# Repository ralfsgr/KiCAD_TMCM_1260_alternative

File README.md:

# KiCAD_TMCM_1260_alternative
KiCad

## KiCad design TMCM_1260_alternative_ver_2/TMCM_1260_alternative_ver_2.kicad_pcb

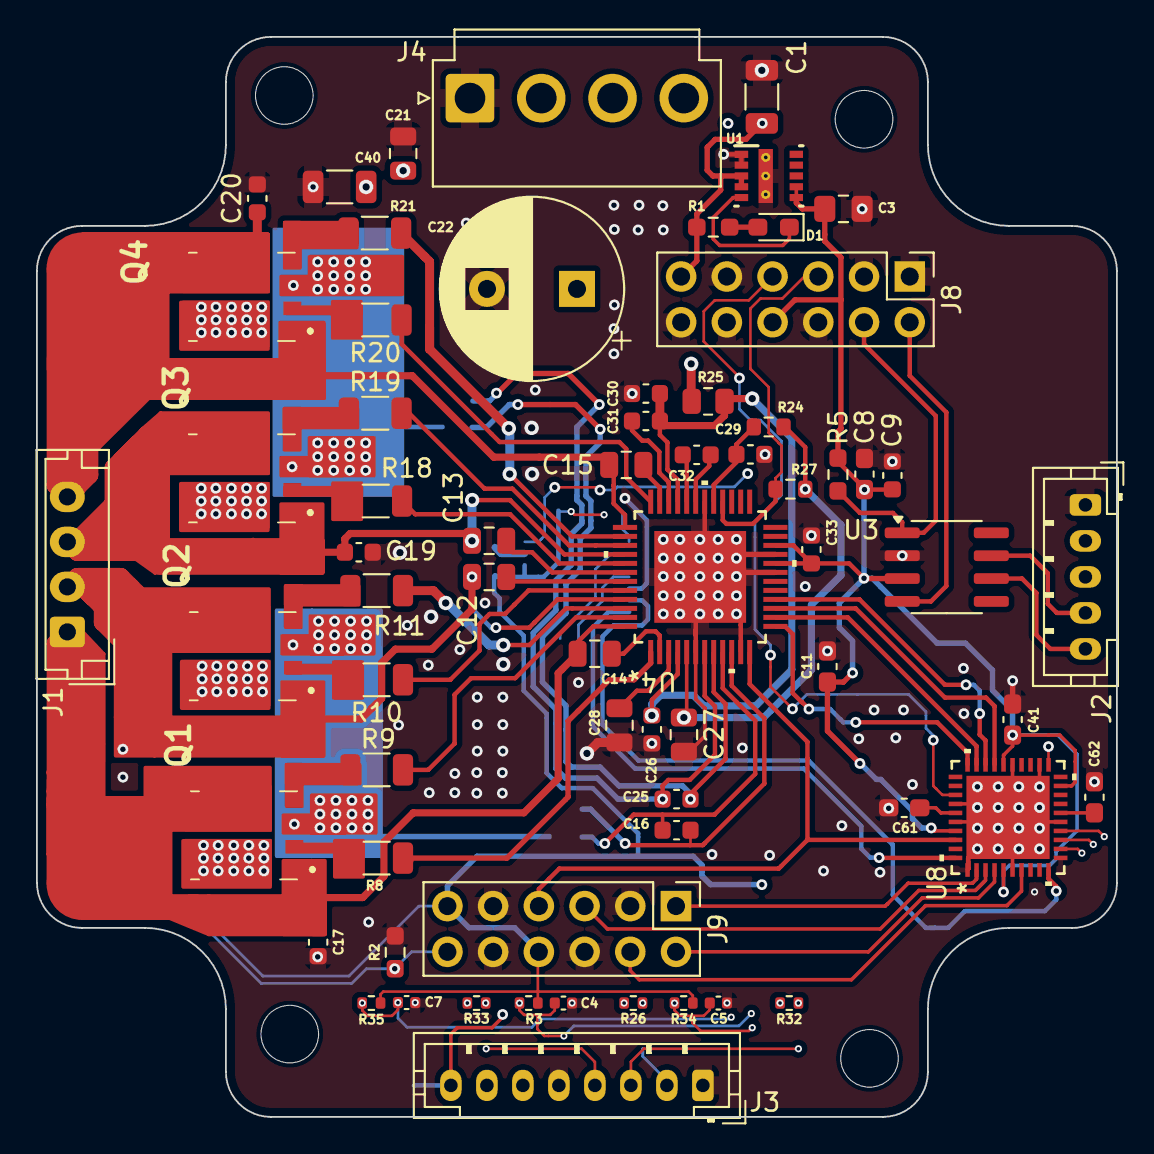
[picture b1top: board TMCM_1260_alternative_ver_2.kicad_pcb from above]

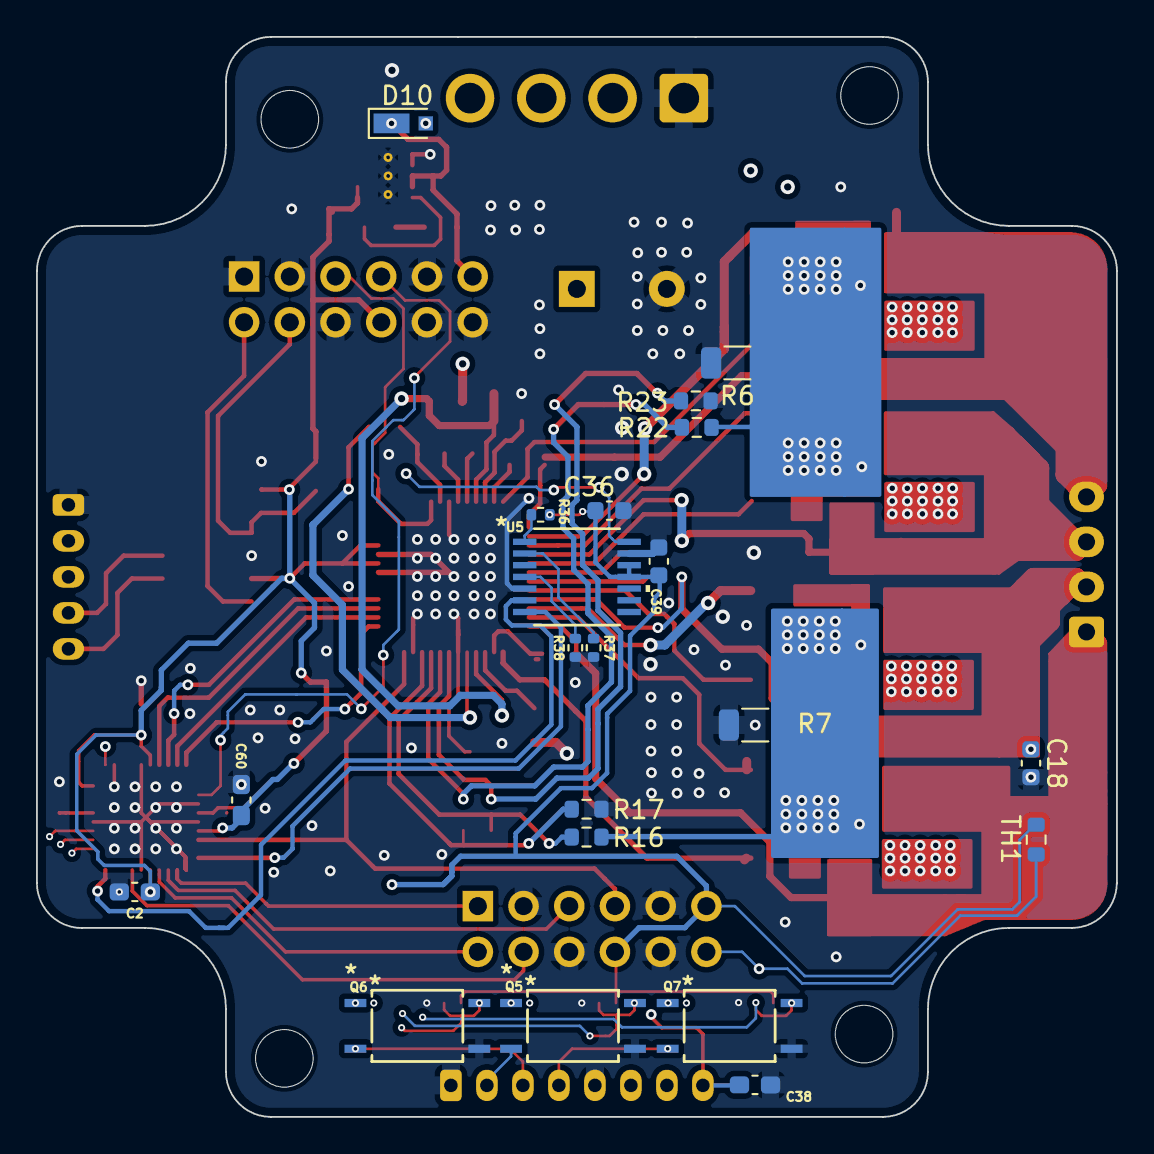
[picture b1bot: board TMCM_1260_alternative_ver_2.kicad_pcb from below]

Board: 4 copper layers, 60.0 x 60.0 mm, 87 parts (21 on the bottom side), 76 nets.

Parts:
C1: 10uF; C_1206_3216Metric
C2, C8, C11, C38, C41, C60, C61, C62: 0.1u; C_0603_1608Metric_Pad1.08x0.95mm_HandSolder
C3: 33uF; C_0805_2012Metric_Pad1.18x1.45mm_HandSolder
C4, C5, C7: 0.1u; C_0402_1005Metric
C9, C39: 1u; C_0603_1608Metric
C12, C13, C14, C15: 470nF; C_0805_2012Metric
C16, C25: 2n2; C_0603_1608Metric
C17, C18, C19, C20: 1n, 100V; C_0603_1608Metric
C21: 4u7; C_0805_2012Metric
C22: 330u; CP_Radial_D10.0mm_P5.00mm
C26, C36: 100n; C_0603_1608Metric
C27, C28: 10u; C_0805_2012Metric
C29, C30, C33: 470n; C_0603_1608Metric
C31: 100n, 16V; C_0603_1608Metric
C32: 22n, 100V; C_0603_1608Metric
C40: 47u; C_1206_3216Metric
D1: LED_RED; D_0603_1608Metric_Pad1.05x0.95mm_HandSolder
D10: D_Schottky; D_MicroSMP_AK
J1: Motor; JST_EH_B4B-EH-A_1x04_P2.50mm_Vertical
J2: CAN; JST_PH_B5B-PH-K_1x05_P2.00mm_Vertical
J3: I/O; JST_PH_B8B-PH-K_1x08_P2.00mm_Vertical
J4: Power; JST_VH_B4P-VH_1x04_P3.96mm_Vertical
J8, J9: Conn_02x06_Odd_Even; PinHeader_2x06_P2.54mm_Vertical
Q1, Q2, Q3, Q4: NVMFD5C650NLT1G; NVMFD5C446NLWFT1G
Q5, Q6, Q7: TLP185GR-TPL_SE; TLP185_GR_TPL_SE
R1: 2k; R_0603_1608Metric_Pad0.98x0.95mm_HandSolder
R2: 10k; R_0603_1608Metric_Pad0.98x0.95mm_HandSolder
R3, R34, R35, R36, R37, R38: 4k7; R_0402_1005Metric
R5: 4k7; R_0603_1608Metric_Pad0.98x0.95mm_HandSolder
R6, R7: 0.075; R_1206_3216Metric
R8, R9, R10, R11, R18, R19, R20, R21: 15; R_1206_3216Metric
R16, R17, R22, R23: 47; R_0603_1608Metric
R24: 2R2; R_0603_1608Metric
R25: 1R; R_0805_2012Metric
R26, R32, R33: 24k; R_0402_1005Metric
R27: 4k7; R_0603_1608Metric
TH1: Thermistor_NTC; R_0603_1608Metric
U1: LMZM23600V3SILR
U3: TCAN337; SOIC-8_3.9x4.9mm_P1.27mm
U4: TMC5160A-TA-T; TMC5160A_TA_T
U5: AS5047P-ATSM; AS5047P_ATSM
U8: TMC4361A-LA-T; TMC4361A_LA_T

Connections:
5VOUT: C27.1, C38.1, J3.8, R24.1, R27.1, U4.5 (5VOUT)
12-36V: C21.1, C22.1, C40.1, D10.2 (A), J3.6, J3.7, J4.2, J4.3, Q1.7 (D1_1), Q1.8 (D1_2), Q1.9 (D1_3), Q1.10 (D1_4), Q1.14, Q2.7 (D1_1), Q2.8 (D1_2), Q2.9 (D1_3), Q2.10 (D1_4), Q2.14, Q3.7 (D1_1), Q3.8 (D1_2), Q3.9 (D1_3), Q3.10 (D1_4), Q3.14, Q4.7 (D1_1), Q4.8 (D1_2), Q4.9 (D1_3), Q4.10 (D1_4), Q4.14, R25.1, R26.2, R32.2, R33.2
/CANH: J2.4, U3.7 (CANH)
/CANL: J2.5, U3.6 (CANL)
/RXD: J8.2, U3.4 (RXD)
/TXD: J8.4, R5.1, U3.1 (TXD)
BMA1: C13.2, C19.1, J1.3, Q3.1 (S1), Q3.5 (D2_1), Q3.6 (D2_2), Q3.11 (D2_3), Q3.12 (D2_4), Q3.13, U4.40 (BMA1)
BMA2: C15.2, C20.1, J1.4, Q4.1 (S1), Q4.5 (D2_1), Q4.6 (D2_2), Q4.11 (D2_3), Q4.12 (D2_4), Q4.13, U4.37 (BMA2)
BMB1: C14.2, C17.1, J1.1, Q1.1 (S1), Q1.5 (D2_1), Q1.6 (D2_2), Q1.11 (D2_3), Q1.12 (D2_4), Q1.13, U4.48 (BMB1)
BMB2: C12.2, C18.1, J1.2, Q2.1 (S1), Q2.5 (D2_1), Q2.6 (D2_2), Q2.11 (D2_3), Q2.12 (D2_4), Q2.13, U4.45 (BMB2)
CA1: C13.1, U4.42 (CA1)
CA2: C15.1, U4.35 (CA2)
CB1: C14.1, U4.2 (CB1)
CB2: C12.1, U4.43 (CB2)
CLK_EXT: J9.7, U4.12 (CLK), U8.38 (CLK_EXT)
CPI: C32.1, U4.32 (CPI)
CPO: C32.2, U4.31 (CPO)
CSN: J9.1, U8.2 (NSCSIN)
CSN_DRV: U4.13 (CSN_CFG3), U8.30 (NSCSDRV_SDO)
DRV_ENN: J8.5, R27.2, U4.28 (DRV_ENN)
GND: C1.2, C2.2, C3.2, C4.2, C5.2, C7.2, C8.2, C9.2, C11.2, C17.2, C18.2, C19.2, C20.2, C21.2, C22.2, C26.2, C27.2, C28.2, C29.2, C30.1, C33.2, C36.1, C38.2, C39.1, C40.2, C41.1, C60.1, C61.1, C62.1, J2.1, J3.1, J3.5, J4.1, J8.1, J8.3, J8.6, J8.9, J8.10, J8.12, J9.3, J9.6, J9.9, J9.10, Q5.4, Q6.4, Q7.4, R2.1, R6.2, R7.2, R17.1, R23.1, R37.2, R38.2, U1.1 (GND), U1.2 (MODE_SYNC), U1.11 (PAD), U1.PAD, U3.2 (GND), U4.6 (GNDA), U4.11 (TST_MODE), U4.19 (GNDD), U4.21 (SD_MODE), U4.30 (GNDD), U4.49 (GNDD/GNDP), U5.5 (TEST), U5.13 (GND), U8.1 (ANEG_NSCLK), U8.6 (GND), U8.11 (BNEG_NSDI), U8.15 (GND), U8.22 (NNEG), U8.25 (GND), U8.34 (TEST_MODE), U8.36 (GND), U8.41
HA1: R18.1, U4.41 (HA1)
HA2: R20.1, U4.36 (HA2)
HB1: R8.1, U4.1 (HB1)
HB2: R10.1, U4.44 (HB2)
HOME_REF: C4.1, Q5.6, R3.1, U8.13 (HOME_REF)
INCR_A: U5.7 (A), U8.40 (A_SCLK)
INCR_B: U5.6 (B), U8.10 (B_SDI)
INCR_I: U5.14 (I/PWM), U8.21 (N)
INTR: J8.7, U8.33 (INTR)
LA1: R19.1, U4.39 (LA1)
LA2: R21.1, U4.38 (LA2)
LB1: R9.1, U4.47 (LB1)
LB2: R11.1, U4.46 (LB2)
unnamed: C61.2, U8.35 (VDD1V8)
unnamed: C62.2, U8.16 (VDD1V8)
unnamed: D1.2 (A), R1.1
unnamed: D1.1 (K), U1.5 (PGOOD)
unnamed: Q1.2 (G1), R8.2
unnamed: Q1.4 (G2), R9.2
unnamed: Q1.3 (S2), Q2.3 (S2), R7.1, R16.1
unnamed: Q2.2 (G1), R10.2
unnamed: Q2.4 (G2), R11.2
unnamed: Q3.2 (G1), R18.2
unnamed: Q3.4 (G2), R19.2
unnamed: Q3.3 (S2), Q4.3 (S2), R6.1, R22.1
unnamed: Q4.2 (G1), R20.2
unnamed: Q4.4 (G2), R21.2
unnamed: Q5.1, R26.1
unnamed: Q6.1, R32.1
unnamed: Q7.1, R33.1
unnamed: C28.1, U4.3 (12VOUT)
unnamed: C29.1, R24.2, U4.29 (VCC)
unnamed: R37.1, U5.2 (CLK)
unnamed: R36.1, U5.1 (CSn)
unnamed: R38.1, U5.4 (MOSI)
Out_1: J3.4, Q7.3
Out_2: J3.3, Q6.3
PGOOD: C1.1, D10.1 (K), J8.11, R1.2, U1.3 (VIN), U1.4 (EN)
SCK: J9.5, U8.3 (SCKIN)
SCK_DRV: U4.14 (SCK_CFG2), U8.29 (SCKDRV_NSDO)
SPI_MISO: J9.4, U8.7 (SDOIN)
SPI_MISO_DRV: U4.16 (SDO_CFG0), U8.28 (SDIDRV_NSCLK)
SPI_MOSI: J9.2, U8.4 (SDIIN)
SPI_MOSI_DRV: U4.15 (SDI_CFG1), U8.27 (SDODRV_SCLK)
SRAH: C25.1, R22.2, U4.8 (SRAH)
SRAL: C25.2, R23.2, U4.7 (SRAL)
SRBH: C16.1, R16.2, U4.9 (SRBH)
SRBL: C16.2, R17.2, U4.10 (SRBL)
STOPL: C7.1, Q7.6, R35.1, U8.12 (STOPL)
STOPR: C5.1, Q6.6, R34.1, U8.14 (STOPR)
VCC_IO: C2.1, C3.1, C8.1, C9.1, C11.1, C33.1, C36.2, C39.2, C41.2, C60.2, J8.8, J9.8, J9.11, R3.2, R5.2, R34.2, R35.2, R36.2, TH1.2, U1.6 (VOUT), U1.7 (FB), U3.3 (VCC), U4.20 (VCC_IO), U4.22 (SPI_MODE), U5.11 (VDD), U5.12 (VDD3V), U8.5 (VCC), U8.19 (NFREEZE), U8.26 (VCC), U8.37 (VCC)
VCP: C31.2, U4.34 (VCP)
VS: C26.1, C30.2, C31.1, R25.2, U4.4 (VSA), U4.33 (VS)
home: J3.2, Q5.3
monitoring: J9.12, R2.2, TH1.1

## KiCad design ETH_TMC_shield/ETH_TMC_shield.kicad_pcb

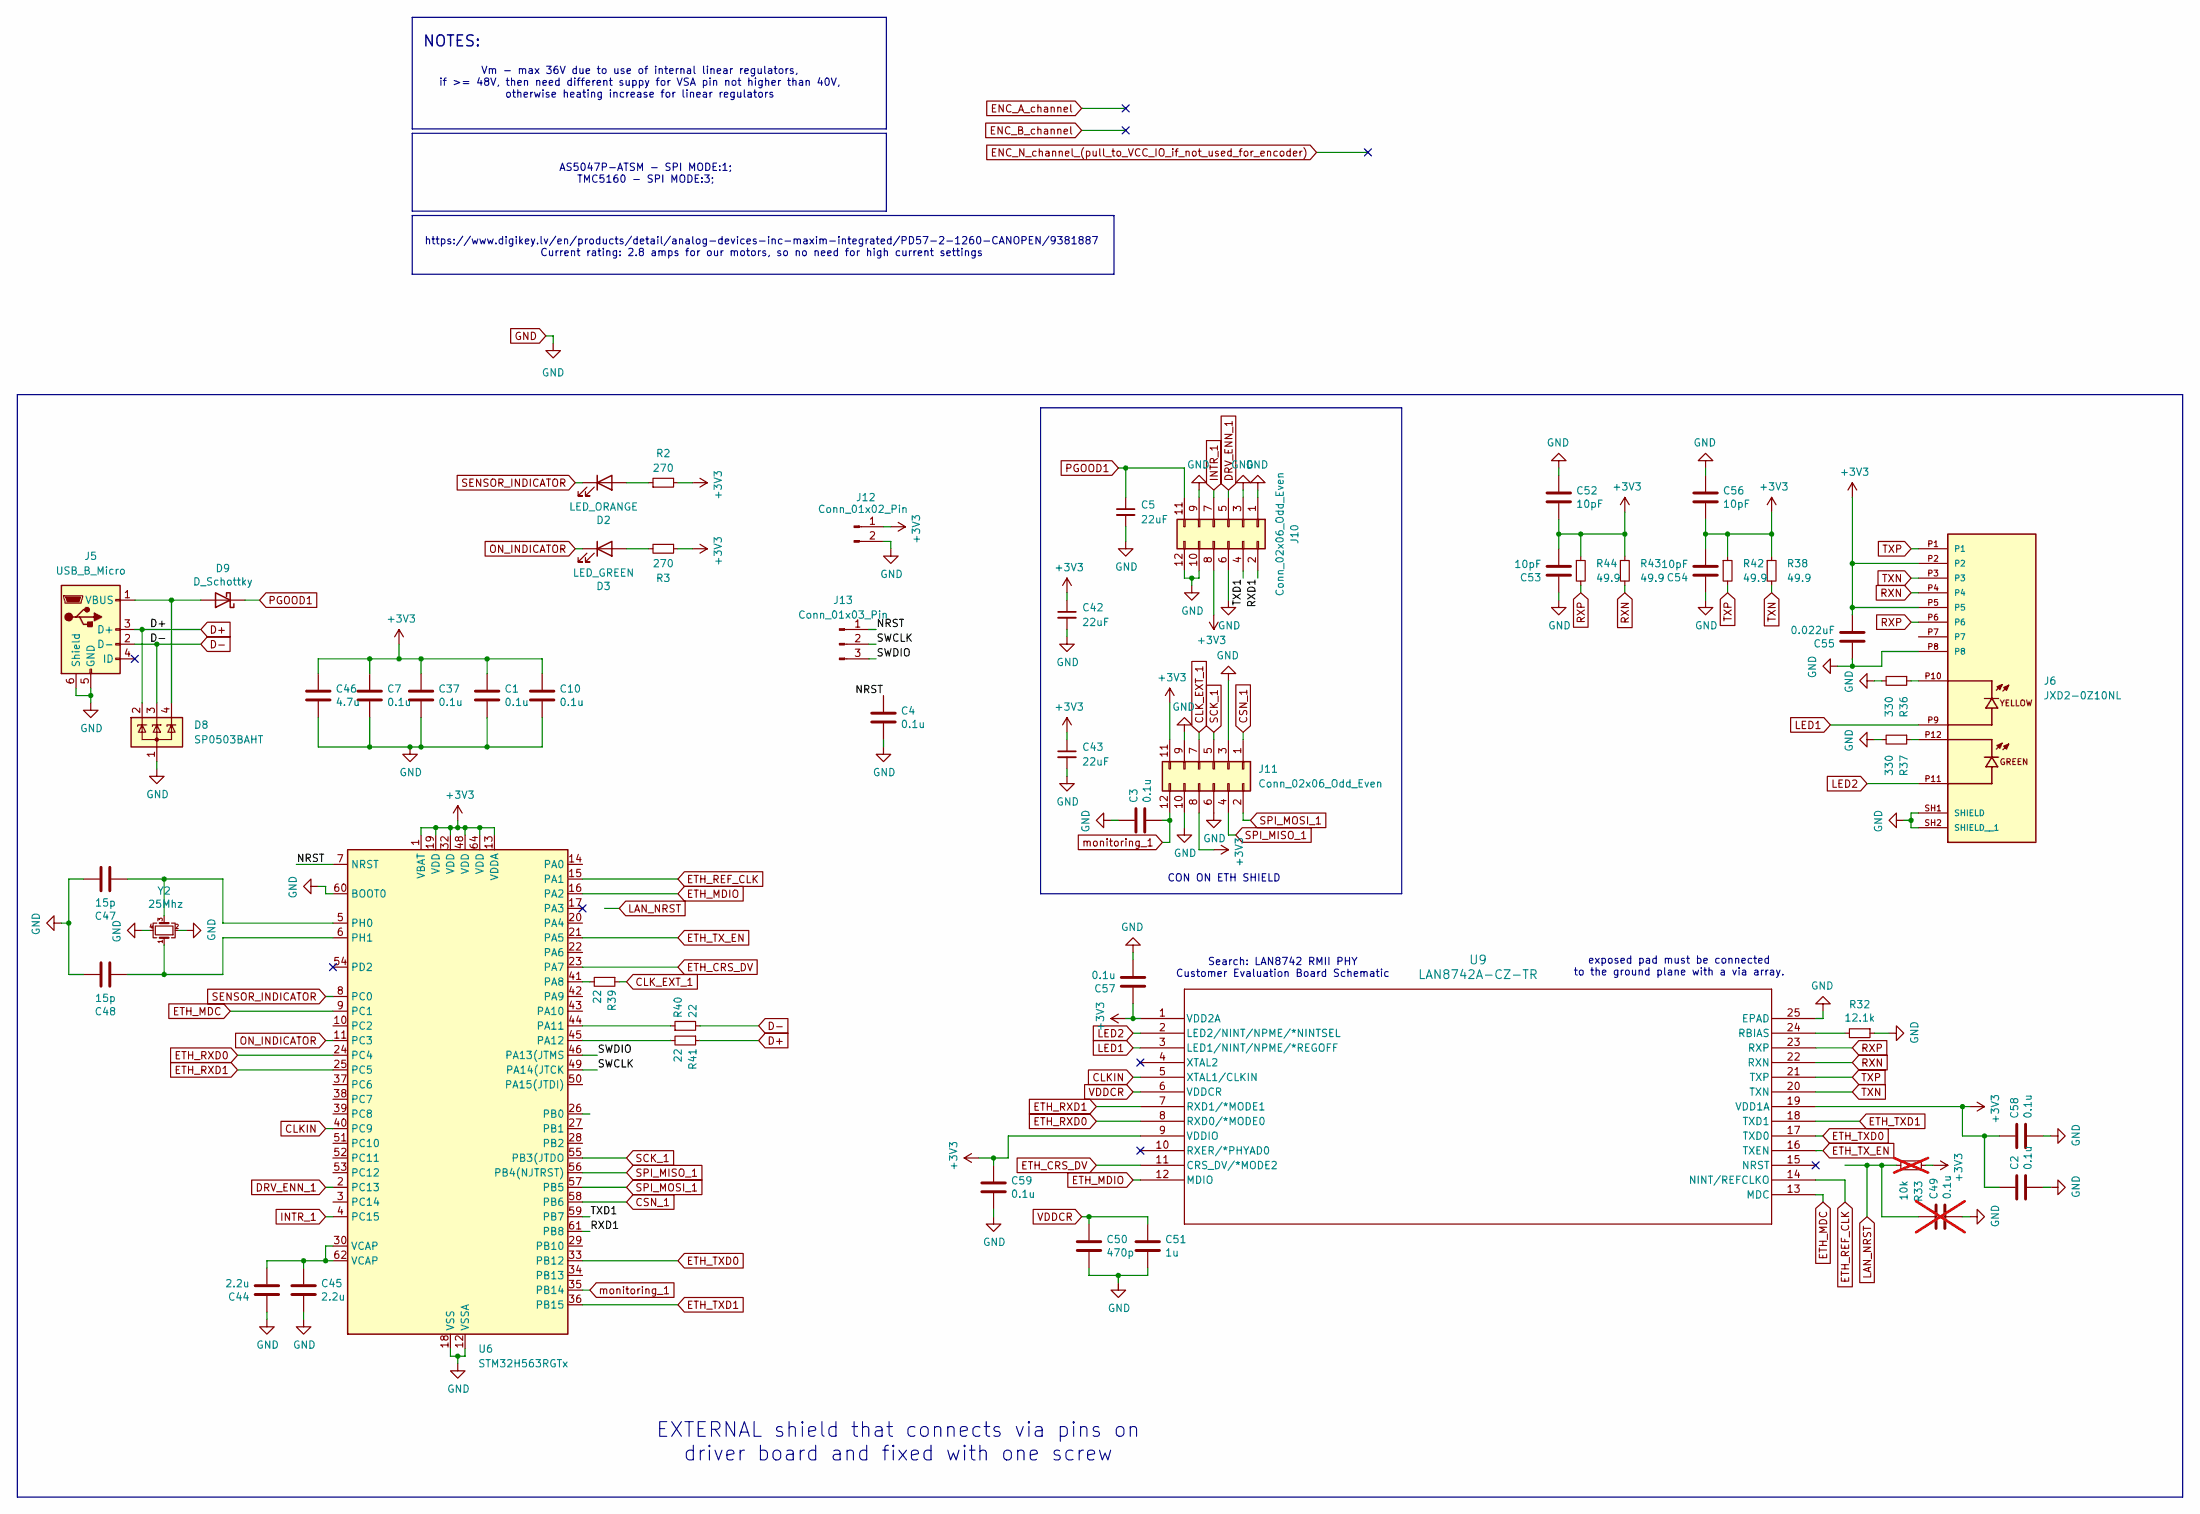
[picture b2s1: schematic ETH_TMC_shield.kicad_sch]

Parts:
C1, C2, C3, C4, C7, C10, C37, C57, C58, C59: 0.1u; C_0402_1005Metric
C5, C42, C43: 22uF; C_0805_2012Metric_Pad1.18x1.45mm_HandSolder
C44, C45: 2.2u; C_0402_1005Metric
C46: 4.7u; C_0402_1005Metric
C47, C48: 15p; C_0603_1608Metric
C49: 0.1u; C_0603_1608Metric_Pad1.08x0.95mm_HandSolder; not fitted
C50: 470p; C_0402_1005Metric
C51: 1u; C_0402_1005Metric
C52, C53, C54, C56: 10pF; C_0603_1608Metric_Pad1.08x0.95mm_HandSolder
C55: 0.022uF; C_0603_1608Metric_Pad1.08x0.95mm_HandSolder
D2: LED_ORANGE; LED_0402_1005Metric
D3: LED_GREEN; D_0402_1005Metric
D8: SP0503BAHT; SOT-143
D9: D_Schottky; D_MicroSMP_AK
J5: USB_B_Micro; USB_Micro-B_Molex-105133-0031
J6: JXD2-0Z10NL; JXD2_0Z10NL; PARTREV 08/23
J10, J11: Conn_02x06_Odd_Even; PinHeader_2x06_P2.54mm_Vertical
J12: Conn_01x02_Pin; PinHeader_1x02_P1.27mm_Vertical
J13: Conn_01x03_Pin; PinHeader_1x03_P1.27mm_Vertical
R2, R3: 270; R_0402_1005Metric
R32: 12.1k; R_0402_1005Metric
R33: 10k; R_0603_1608Metric; not fitted
R36, R37: 330; R_0603_1608Metric
R38, R42, R43, R44: 49.9; R_0603_1608Metric
R39, R40, R41: 22; R_0402_1005Metric
U6: STM32H563RGTx; LQFP-64_10x10mm_P0.5mm
U9: LAN8742A-CZ-TR; LAN8742A_CZ_TR
Y2: 25Mhz; Crystal_SMD_2016-4Pin_2.0x1.6mm

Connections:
+3V3: C1.1, C2.1, C7.1, C10.1, C37.1, C42.1, C43.1, C46.1, C52.2, C53.2, C54.2, C55.2, C56.2, C57.1, C58.1, C59.1, J6.P2, J6.P5, J10.8, J11.8, J11.11, J12.1, R2.2, R3.1, R33.1, R38.1, R42.1, R43.1, R44.1, U6.1 (VBAT), U6.13 (VDDA), U6.19 (VDD), U6.32 (VDD), U6.48 (VDD), U6.64 (VDD), U9.1 (VDD2A), U9.9 (VDDIO), U9.19 (VDD1A)
/NRST: C4.1, J13.1, U6.7 (NRST)
/RXD1: J10.2, U6.61 (PB8)
/SWCLK: J13.2, U6.49 (PA14(JTCK)
/SWDIO: J13.3, U6.46 (PA13(JTMS)
/TXD1: J10.4, U6.59 (PB7)
CLKIN: U6.40 (PC9), U9.5 (XTAL1/CLKIN)
CLK_EXT_1: J11.7, R39.1
CSN_1: J11.1, U6.58 (PB6)
D+: D8.2 (K), J5.3 (D+), R41.1
D-: D8.3 (K), J5.2 (D-), R40.2
DRV_ENN_1: J10.5, U6.2 (PC13)
ETH_CRS_DV: U6.23 (PA7), U9.11 (CRS_DV/*MODE2)
ETH_MDC: U6.9 (PC1), U9.13 (MDC)
ETH_MDIO: U6.16 (PA2), U9.12 (MDIO)
ETH_REF_CLK: U6.15 (PA1), U9.14 (NINT/REFCLKO)
ETH_RXD0: U6.24 (PC4), U9.8 (RXD0/*MODE0)
ETH_RXD1: U6.25 (PC5), U9.7 (RXD1/*MODE1)
ETH_TXD0: U6.33 (PB12), U9.17 (TXD0)
ETH_TXD1: U6.36 (PB15), U9.18 (TXD1)
ETH_TX_EN: U6.21 (PA5), U9.16 (TXEN)
GND: C1.2, C2.2, C3.1, C4.2, C5.2, C7.2, C10.2, C37.2, C42.2, C43.2, C44.1, C45.2, C46.2, C47.1, C48.1, C49.2, C50.2, C51.2, C52.1, C53.1, C54.1, C55.1, C56.1, C57.2, C58.2, C59.2, D8.1 (A), J5.5 (GND), J5.6 (Shield), J6.P8, J6.SH1 (SHIELD), J6.SH2 (SHIELD__1), J10.1, J10.3, J10.6, J10.9, J10.10, J10.12, J11.3, J11.6, J11.9, J11.10, J12.2, R32.1, R36.2, R37.2, U6.12 (VSSA), U6.18 (VSS), U6.31 (VSS), U6.47 (VSS), U6.60 (BOOT0), U6.63 (VSS), U9.25 (EPAD), Y2.2, Y2.4
INTR_1: J10.7, U6.4 (PC15)
LED1: J6.P9, U9.3 (LED1/NINT/NPME/*REGOFF)
LED2: J6.P11, U9.2 (LED2/NINT/NPME/*NINTSEL)
unnamed: C44.2, C45.1, U6.30 (VCAP), U6.62 (VCAP)
unnamed: C49.1, R33.2
unnamed: D2.2 (A), R2.1
unnamed: D3.2 (A), R3.2
unnamed: D8.4 (K), D9.2 (A), J5.1 (VBUS)
unnamed: J6.P10, R36.1
unnamed: J6.P12, R37.1
unnamed: R39.2, U6.41 (PA8)
unnamed: R40.1, U6.44 (PA11)
unnamed: R41.2, U6.45 (PA12)
unnamed: C47.2, U6.5 (PH0), Y2.3
unnamed: C48.2, U6.6 (PH1), Y2.1
unnamed: R32.2, U9.24 (RBIAS)
ON_INDICATOR: D3.1 (K), U6.11 (PC3)
PGOOD1: C5.1, D9.1 (K), J10.11
RXN: J6.P4, R43.2, U9.22 (RXN)
RXP: J6.P6, R44.2, U9.23 (RXP)
SCK_1: J11.5, U6.55 (PB3(JTDO)
SENSOR_INDICATOR: D2.1 (K), U6.8 (PC0)
SPI_MISO_1: J11.4, U6.56 (PB4(NJTRST))
SPI_MOSI_1: J11.2, U6.57 (PB5)
TXN: J6.P3, R38.2, U9.20 (TXN)
TXP: J6.P1, R42.2, U9.21 (TXP)
VDDCR: C50.1, C51.1, U9.6 (VDDCR)
monitoring_1: C3.2, J11.12, U6.35 (PB14)

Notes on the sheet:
AS5047P-ATSM - SPI MODE:1; TMC5160 - SPI MODE:3;
exposed pad must be connected to the ground plane with a via array.
CON ON ETH SHIELD
Search: LAN8742 RMII PHY Customer Evaluation Board Schematic
EXTERNAL shield that connects via pins on driver board and fixed with one screw
NOTES:
Vm - max 36V due to use of internal linear regulators, if >= 48V, then need different suppy for VSA pin not higher than 40V, otherwise heating increase for linear regulators
https://www.digikey.lv/en/products/detail/analog-devices-inc-maxim-integrated/PD57-2-1260-CANOPEN/9381887 Current rating: 2.8 amps for our motors, so no need for high current settings

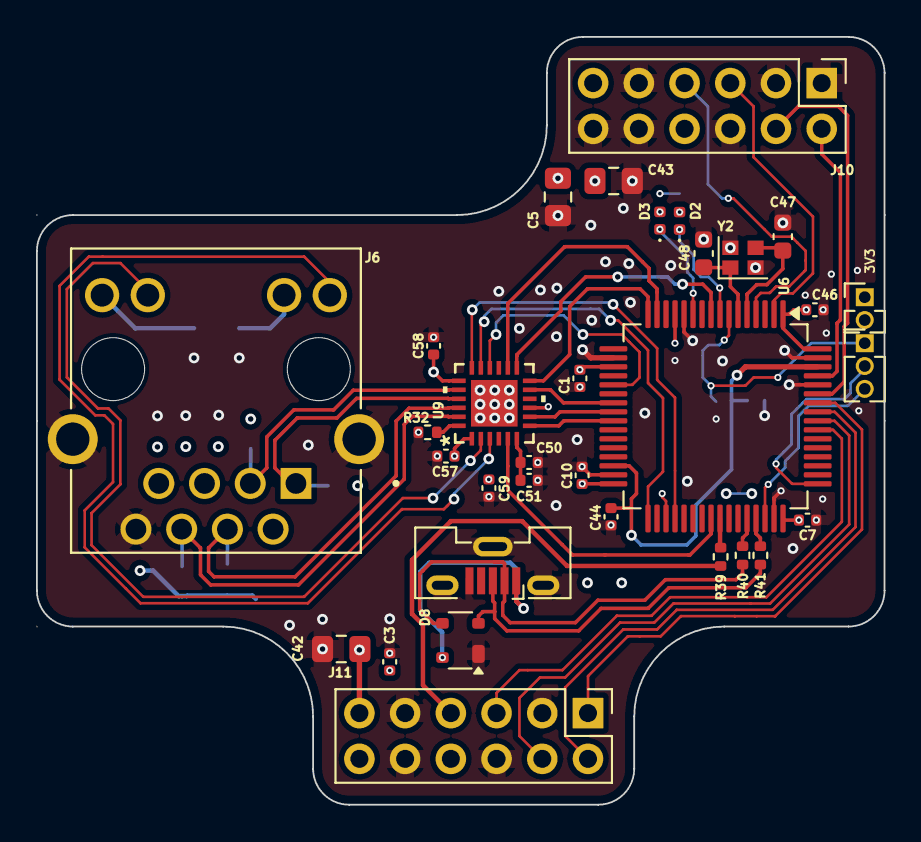
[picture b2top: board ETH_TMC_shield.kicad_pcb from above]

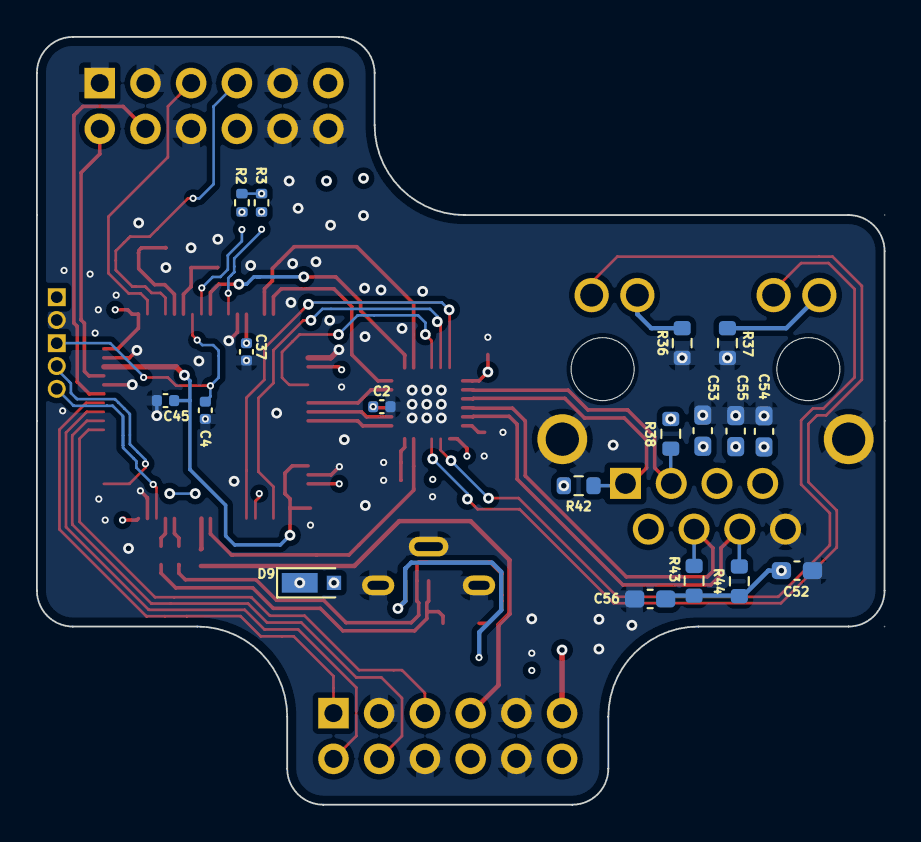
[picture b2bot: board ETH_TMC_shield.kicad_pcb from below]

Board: 4 copper layers, 47.1 x 42.7 mm, 50 parts (18 on the bottom side), 49 nets.

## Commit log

2025-12-11 not finished
2025-12-23 not_finished
2025-12-29 finished
2026-01-27 iterration 2 upload
2026-01-27 second version started
2026-01-27 upload
2026-02-04 tmc4361 added ver_2
2026-02-04 internal stm32 usb added
2026-02-07 ver 2 design not finished
2026-02-08 ver2 not finished
2026-02-10 not finish
2026-02-11 not ready
2026-02-12 finished not checked
2026-02-17 absolute encoder SPI switched to ABI incremental
